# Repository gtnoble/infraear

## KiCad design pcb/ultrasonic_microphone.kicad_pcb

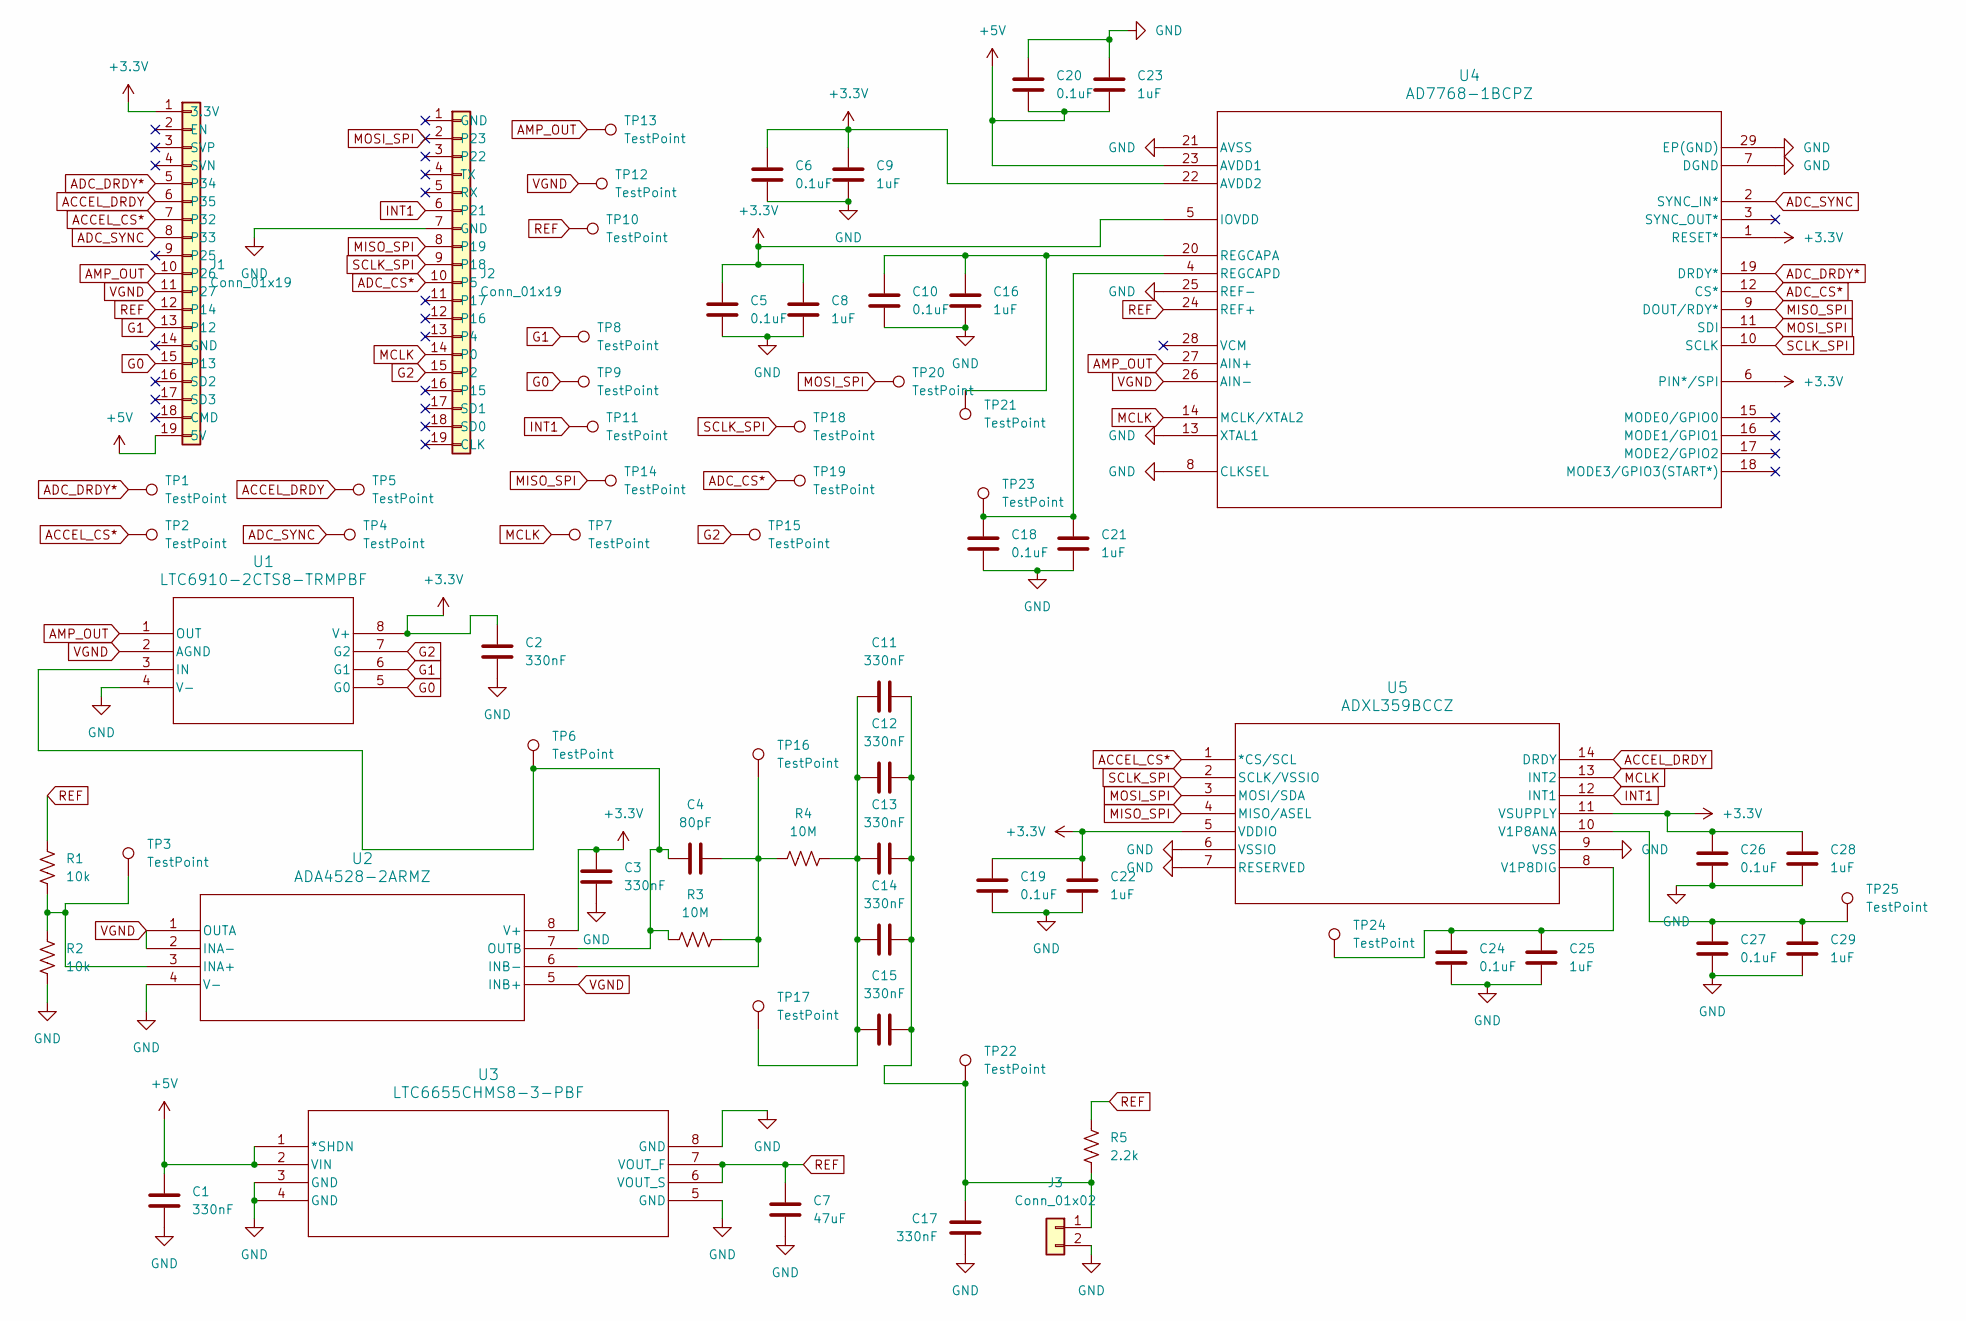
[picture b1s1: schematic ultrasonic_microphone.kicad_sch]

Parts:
C1, C2, C3, C11, C12, C13, C14, C15, C17: 330nF; C_1206_3216Metric_Pad1.33x1.80mm_HandSolder
C4: 80pF; C_0805_2012Metric_Pad1.18x1.45mm_HandSolder
C5, C6, C10, C18, C19, C20, C24, C26, C27: 0.1uF; C_0805_2012Metric_Pad1.18x1.45mm_HandSolder
C7: 47uF; C_0805_2012Metric_Pad1.18x1.45mm_HandSolder
C8, C9, C16, C21, C22, C23, C25, C28, C29: 1uF; C_0805_2012Metric_Pad1.18x1.45mm_HandSolder
J1, J2: Conn_01x19; PinSocket_1x19_P2.54mm_Vertical
J3: Conn_01x02; PinHeader_1x02_P2.54mm_Horizontal
R1, R2: 10k; R_0805_2012Metric_Pad1.20x1.40mm_HandSolder
R3, R4: 10M; R_0805_2012Metric_Pad1.20x1.40mm_HandSolder
R5: 2.2k; C_0805_2012Metric_Pad1.18x1.45mm_HandSolder
TP1, TP2, TP3, TP4, TP5, TP6, TP7, TP8, TP9, TP10, TP11, TP12, TP13, TP14, TP15, TP16, TP17, TP18, TP19, TP20, TP21, TP22, TP23, TP24, TP25: TestPoint; TestPoint_Pad_D1.5mm
U1: LTC6910-2CTS8-TRMPBF; TSOT-23_TS8_LIT
U2: ADA4528-2ARMZ; RM_8_ADI
U3: LTC6655CHMS8-3-PBF; MSOP-8_MS_LIT
U4: AD7768-1BCPZ; CP_28_12
U5: ADXL359BCCZ; LGA14_CC-14-2_ADI

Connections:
+3.3V: C2.1, C3.1, C5.1, C6.1, C8.1, C9.1, C19.1, C22.1, C26.1, C28.1, J1.1 (3.3V), U1.8 (V+), U2.8 (V+), U4.1 (RESET*), U4.5 (IOVDD), U4.6 (PIN*/SPI), U4.22 (AVDD2), U5.5 (VDDIO), U5.11 (VSUPPLY)
+5V: C1.1, C20.2, C23.2, J1.19 (5V), U3.1 (*SHDN), U3.2 (VIN), U4.23 (AVDD1)
ACCEL_CS*: J1.7 (P32), TP2.1, U5.1 (*CS/SCL)
ACCEL_DRDY: J1.6 (P35), TP5.1, U5.14 (DRDY)
ADC_CS*: J2.10 (P5), TP19.1, U4.12 (CS*)
ADC_DRDY*: J1.5 (P34), TP1.1, U4.19 (DRDY*)
ADC_SYNC: J1.8 (P33), TP4.1, U4.2 (SYNC_IN*)
AMP_OUT: J1.10 (P26), TP13.1, U1.1 (OUT), U4.27 (AIN+)
G0: J1.15 (P13), TP9.1, U1.5 (G0)
G1: J1.13 (P12), TP8.1, U1.6 (G1)
G2: J2.15 (P2), TP15.1, U1.7 (G2)
GND: C1.2, C2.2, C3.2, C5.2, C6.2, C7.2, C8.2, C9.2, C10.2, C16.2, C17.2, C18.2, C19.2, C20.1, C21.2, C22.2, C23.1, C24.2, C25.2, C26.2, C27.2, C28.2, C29.2, J2.7 (GND), J3.2, R2.2, U1.4 (V-), U2.4 (V-), U3.3 (GND), U3.4 (GND), U3.5 (GND), U3.8 (GND), U4.7 (DGND), U4.8 (CLKSEL), U4.13 (XTAL1), U4.21 (AVSS), U4.25 (REF-), U4.29 (EP(GND)), U5.6 (VSSIO), U5.7 (RESERVED), U5.9 (VSS); also elsewhere on the board
INT1: J2.6 (P21), TP11.1, U5.12 (INT1)
MCLK: J2.14 (P0), TP7.1, U4.14 (MCLK/XTAL2), U5.13 (INT2)
MISO_SPI: J2.8 (P19), TP14.1, U4.9 (DOUT/RDY*), U5.4 (MISO/ASEL)
MOSI_SPI: J2.2 (P23), TP20.1, U4.11 (SDI), U5.3 (MOSI/SDA)
unnamed: C11.1, C12.1, C13.1, C14.1, C15.1, R4.2, TP17.1
unnamed: C11.2, C12.2, C13.2, C14.2, C15.2, C17.1, J3.1, R5.2, TP22.1
unnamed: C4.1, R3.2, TP6.1, U1.3 (IN), U2.7 (OUTB)
unnamed: R1.2, R2.1, TP3.1, U2.3 (INA+)
unnamed: C4.2, R3.1, R4.1, TP16.1, U2.6 (INB-)
unnamed: C10.1, C16.1, TP21.1, U4.20 (REGCAPA)
unnamed: C18.1, C21.1, TP23.1, U4.4 (REGCAPD)
unnamed: C27.1, C29.1, TP25.1, U5.10 (V1P8ANA)
unnamed: C24.1, C25.1, TP24.1, U5.8 (V1P8DIG)
REF: C7.1, J1.12 (P14), R1.1, R5.1, TP10.1, U3.6 (VOUT_S), U3.7 (VOUT_F), U4.24 (REF+)
SCLK_SPI: J2.9 (P18), TP18.1, U4.10 (SCLK), U5.2 (SCLK/VSSIO)
VGND: J1.11 (P27), TP12.1, U1.2 (AGND), U2.1 (OUTA), U2.2 (INA-), U2.5 (INB+), U4.26 (AIN-)

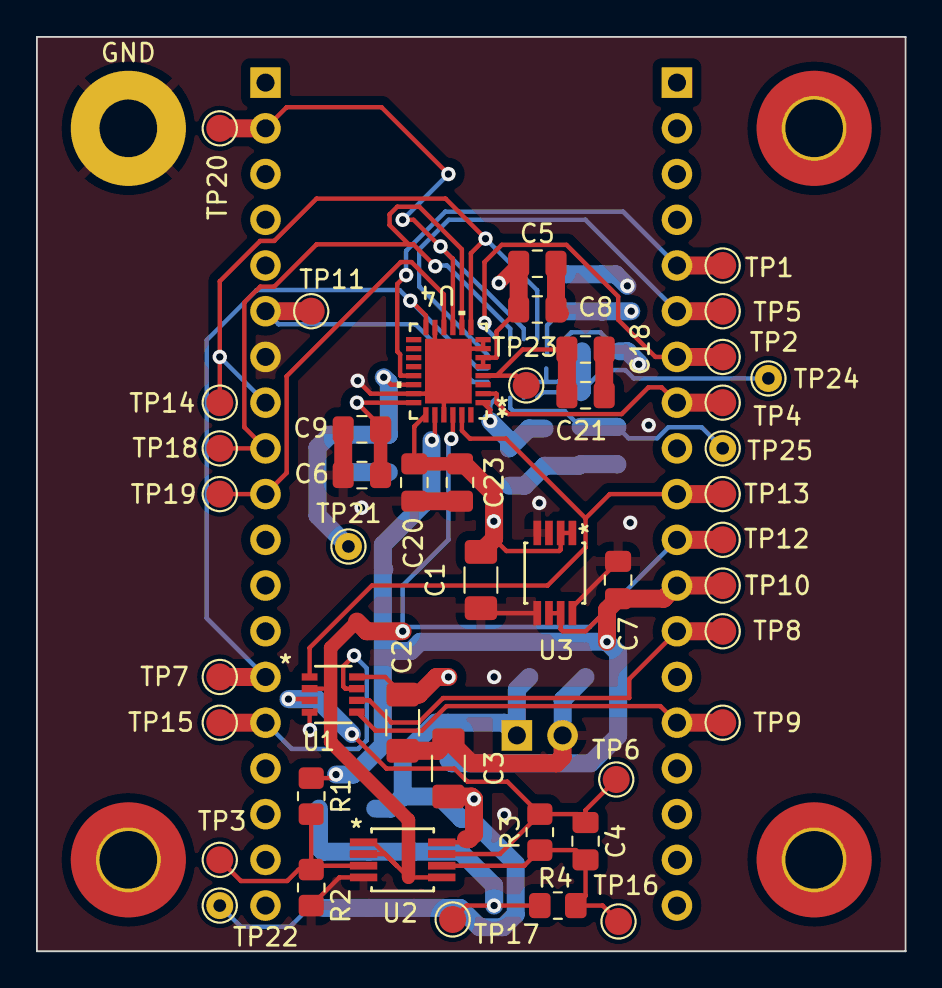
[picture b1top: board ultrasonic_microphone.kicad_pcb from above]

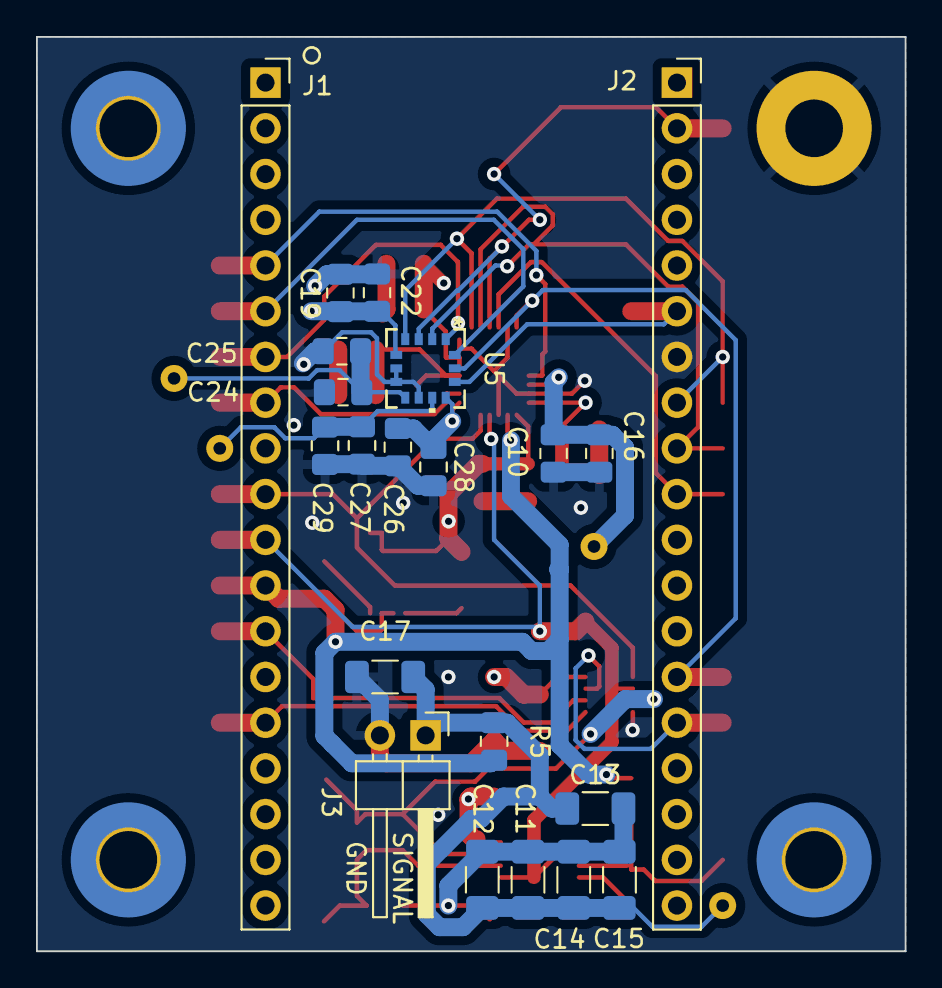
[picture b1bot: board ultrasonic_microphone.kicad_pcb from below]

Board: 4 copper layers, 48.3 x 50.8 mm, 68 parts (21 on the bottom side), 28 nets.

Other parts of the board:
GND: MountingHole_3.2mm_M3_Pad

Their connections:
GND: GND.1; also elsewhere on the board

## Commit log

2023-12-14 Reorganized project. Pcb complete
2024-01-09 Fabbed board
2024-01-09 removing zipped gerbers from repo
2024-01-09 removing backups
2024-01-09 Fabbed gerbers
2024-01-09 Reorgainzed spice files
2024-01-12 Started writing code. ADC MCLK generation, VGA gain set, and Diagnostic inputs work.
2024-01-14 Reading from adc now works
2024-01-16 Wifi now connects
2024-01-16 Added telemetry functionality. not tested
2024-01-16 update project name
2024-01-19 ADC readings now workk!!!
